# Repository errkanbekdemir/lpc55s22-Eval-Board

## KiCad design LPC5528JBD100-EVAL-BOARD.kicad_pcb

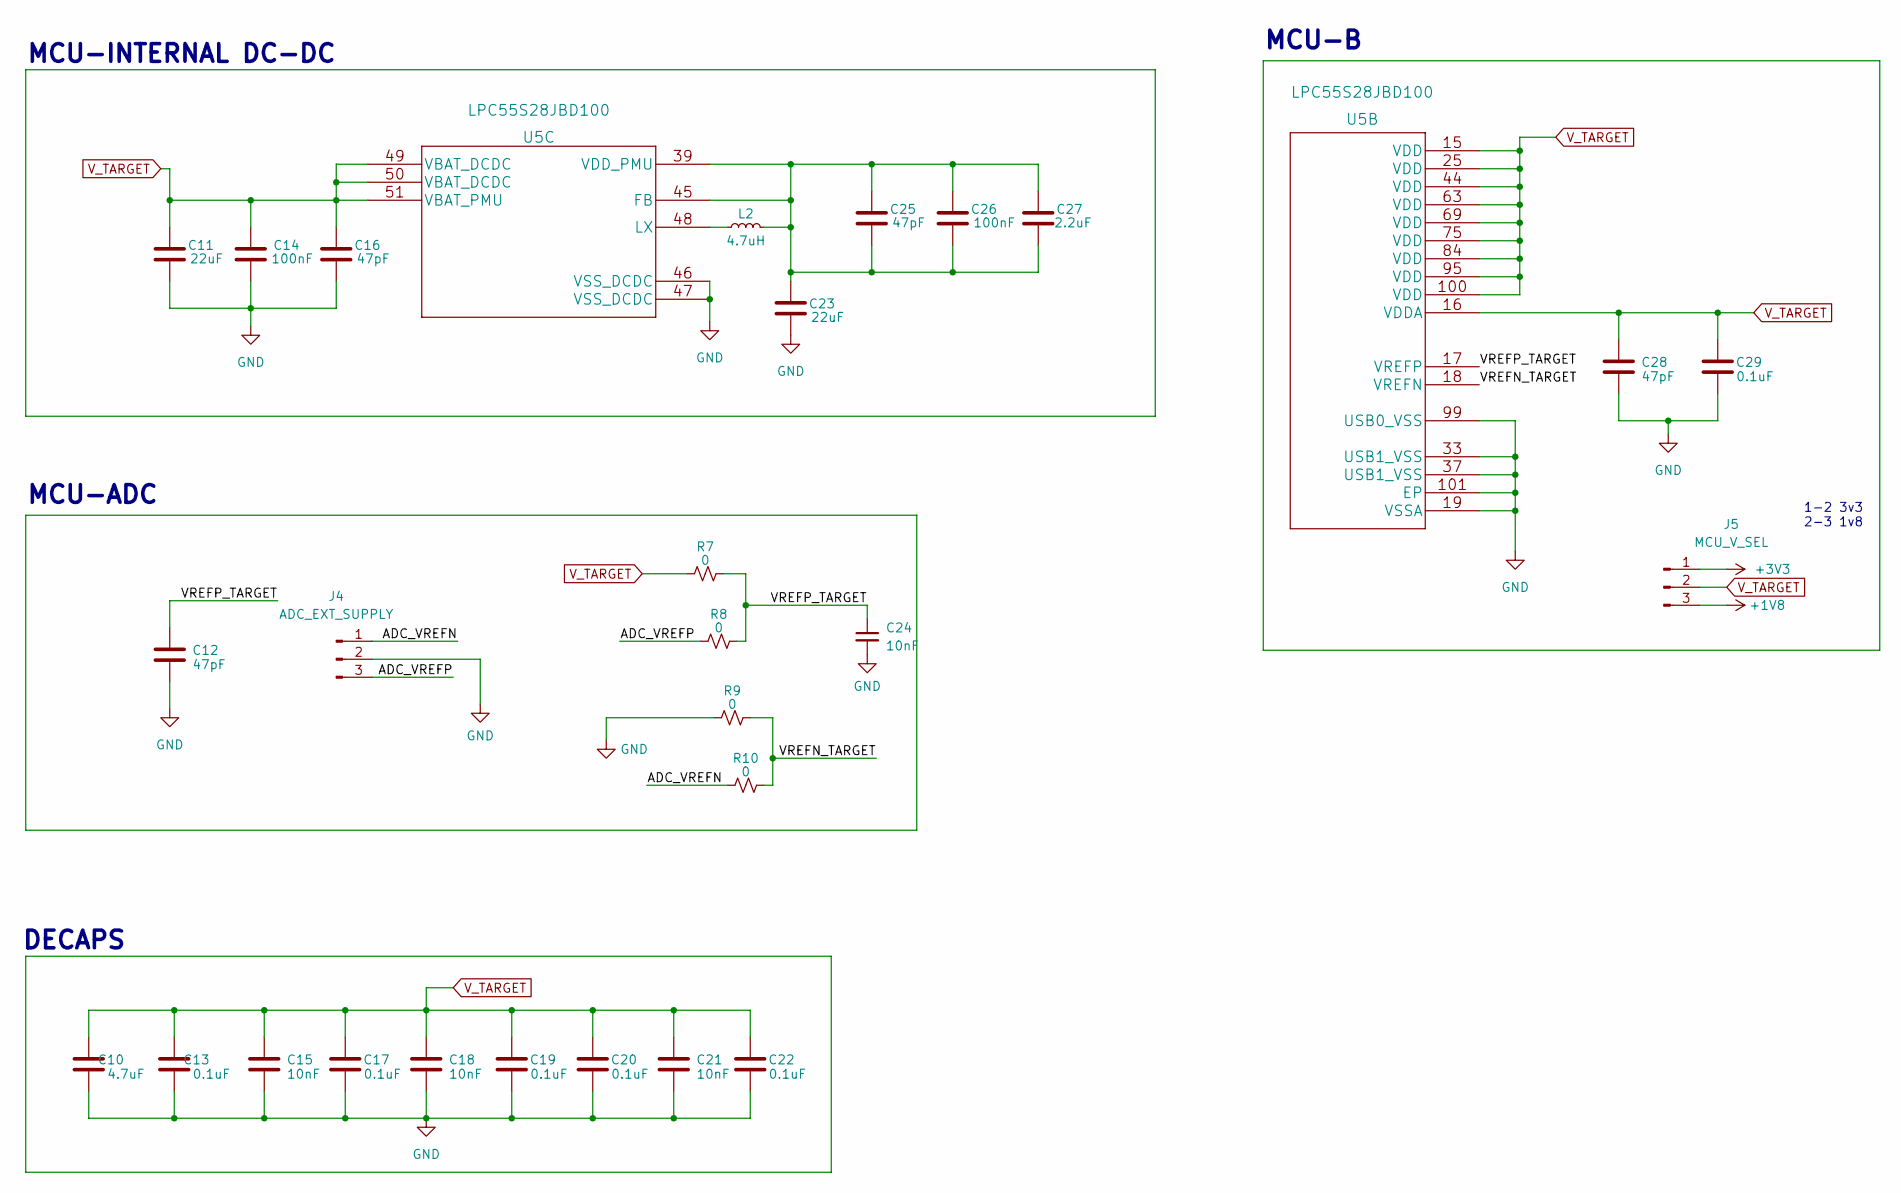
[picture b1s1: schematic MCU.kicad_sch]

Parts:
C10: 4.7uF; C_0603_1608Metric
C11, C23: 22uF; C_0603_1608Metric
C12: 47pF; R_0603_1608Metric
C13, C17, C19, C20, C22, C29: 0.1uF; C_0603_1608Metric
C14, C26: 100nF; C_0603_1608Metric
C15, C18, C21, C24: 10nF; C_0603_1608Metric
C16, C25, C28: 47pF; C_0603_1608Metric
C27: 2.2uF; C_0603_1608Metric
J4: ADC_EXT_SUPPLY; PinHeader_1x03_P2.54mm_Vertical
J5: MCU_V_SEL; PinHeader_1x03_P2.54mm_Vertical
L2: 4.7uH; L_0805_2012Metric
R7, R8, R9, R10: 0; R_0603_1608Metric
U5: LPC55S28JBD100; HLQFP100

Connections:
+1V8: J5.3; also elsewhere on the board
+3V3: J5.1; also elsewhere on the board
/MCU/ADC_VREFN: J4.1, R10.1
/MCU/ADC_VREFP: J4.3, R8.1
/MCU/VREFN_TARGET: R9.2, R10.2, U5.18 (VREFN)
/MCU/VREFP_TARGET: C12.1, C24.1, R7.2, R8.2, U5.17 (VREFP)
GND: C10.2, C11.2, C12.2, C13.2, C14.2, C15.2, C16.2, C17.2, C18.2, C19.2, C20.2, C21.2, C22.2, C23.2, C24.2, C28.2, C29.2, J4.2, R9.1, U5.19 (VSSA), U5.33 (USB1_VSS), U5.37 (USB1_VSS), U5.46 (VSS_DCDC), U5.47 (VSS_DCDC), U5.99 (USB0_VSS), U5.101 (EP); also elsewhere on the board
unnamed: C23.1, C25.1, C25.2, C26.1, C26.2, C27.1, C27.2, L2.2, U5.39 (VDD_PMU), U5.45 (FB)
unnamed: L2.1, U5.48 (LX)
V_TARGET: C10.1, C11.1, C13.1, C14.1, C15.1, C16.1, C17.1, C18.1, C19.1, C20.1, C21.1, C22.1, C28.1, C29.1, J5.2, R7.1, U5.15 (VDD), U5.16 (VDDA), U5.25 (VDD), U5.44 (VDD), U5.49 (VBAT_DCDC), U5.50 (VBAT_DCDC), U5.51 (VBAT_PMU), U5.63 (VDD), U5.69 (VDD), U5.75 (VDD), U5.84 (VDD), U5.95 (VDD), U5.100 (VDD); also elsewhere on the board

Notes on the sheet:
MCU-ADC
MCU-B
DECAPS
MCU-INTERNAL DC-DC
1-2 3v3 2-3 1v8

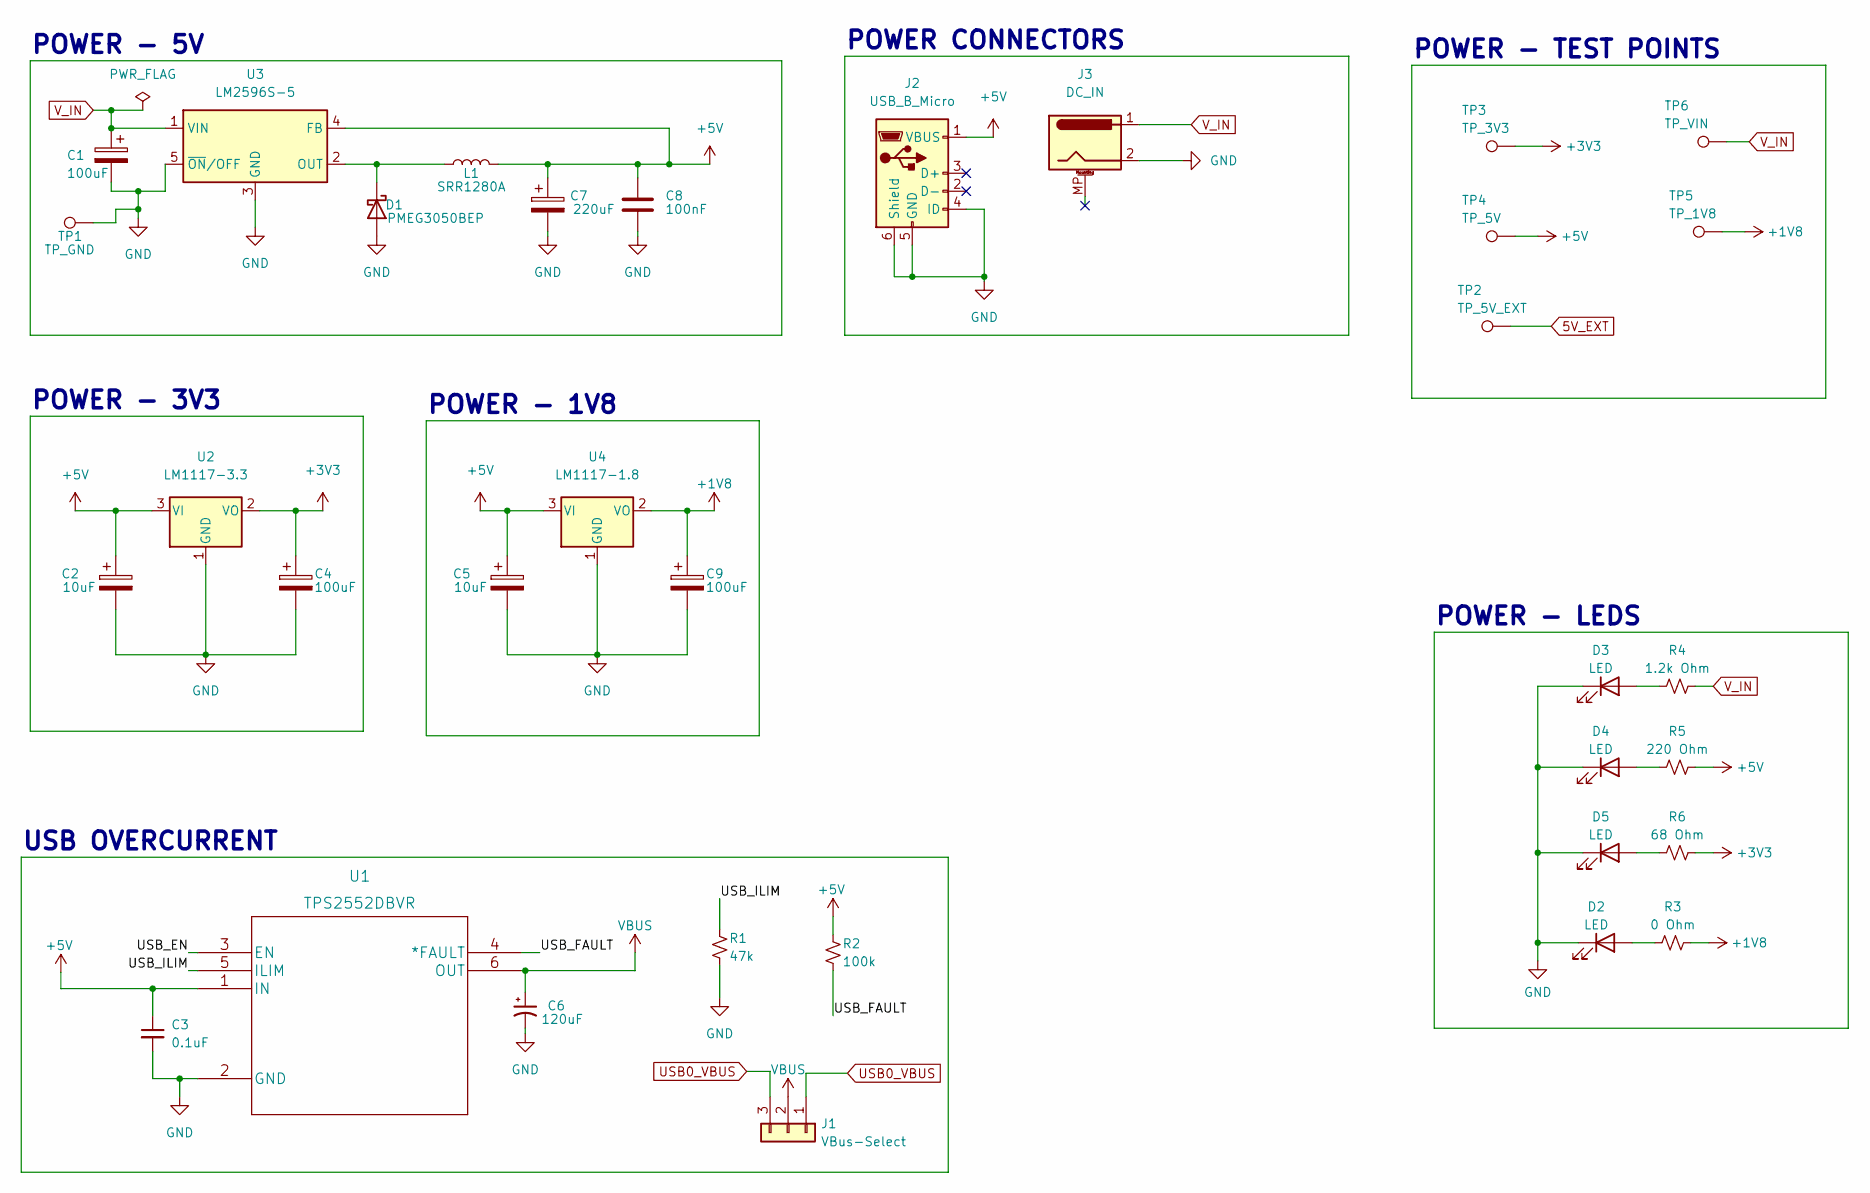
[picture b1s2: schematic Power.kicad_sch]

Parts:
C1: 100uF; CP_Elec_8x10.5
C2, C5: 10uF; CP_EIA-6032-28_Kemet-C
C3: 0.1uF; C_0603_1608Metric
C4, C9: 100uF; CP_EIA-6032-28_Kemet-C
C6: 120uF; CP_EIA-6032-28_Kemet-C
C7: 220uF; CP_EIA-6032-28_Kemet-C
C8: 100nF; C_0603_1608Metric
D1: PMEG3050BEP; D_SOD-128
D2, D3, D4, D5: LED; LED_0805_2012Metric
J1: VBus-Select; PinHeader_1x03_P2.54mm_Vertical
J2: USB_B_Micro; USB_Micro-B_Molex_47346-0001
J3: DC_IN; DC-JACK-5.5x2.1
L1: SRR1280A; L_Bourns_SRR1260
R1: 47k; R_0603_1608Metric
R2: 100k; R_0603_1608Metric
R3: 0 Ohm; R_0603_1608Metric
R4: 1.2k Ohm; R_0603_1608Metric
R5: 220 Ohm; R_0603_1608Metric
R6: 68 Ohm; R_0603_1608Metric
TP1: TP_GND; TestPoint_Pad_D1.0mm
TP2: TP_5V_EXT; TestPoint_Pad_D1.0mm
TP3: TP_3V3; TestPoint_Pad_D1.0mm
TP4: TP_5V; TestPoint_Pad_D1.0mm
TP5: TP_1V8; TestPoint_Pad_D1.0mm
TP6: TP_VIN; TestPoint_Pad_D1.0mm
U1: TPS2552DBVR
U2: LM1117-3.3; SOT-223-3_TabPin2
U3: LM2596S-5; TO-263-5_TabPin3
U4: LM1117-1.8; SOT-223-3_TabPin2

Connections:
5V_EXT: TP2.1
+1V8: C9.1, R3.2, TP5.1, U4.2 (VO); also elsewhere on the board
+3V3: C4.1, R6.2, TP3.1, U2.2 (VO); also elsewhere on the board
+5V: C2.1, C3.1, C5.1, C7.1, C8.1, J2.1 (VBUS), L1.2, R2.1, R5.2, TP4.1, U1.1 (IN), U2.3 (VI), U3.4 (FB), U4.3 (VI)
/Power/USB_EN: U1.3 (EN)
/Power/USB_FAULT: R2.2, U1.4 (*FAULT)
/Power/USB_ILIM: R1.1, U1.5 (ILIM)
GND: C1.2, C2.2, C3.2, C4.2, C5.2, C6.2, C7.2, C8.2, C9.2, D1.2 (A), D2.1 (K), D3.1 (K), D4.1 (K), D5.1 (K), J2.4 (ID), J2.5 (GND), J2.6 (Shield), J3.2, R1.2, TP1.1, U1.2 (GND), U2.1 (GND), U3.3 (GND), U3.5 (~ON/OFF), U4.1 (GND); also elsewhere on the board
unnamed: D1.1 (K), L1.1, U3.2 (OUT)
unnamed: D2.2 (A), R3.1
unnamed: D3.2 (A), R4.1
unnamed: D4.2 (A), R5.1
unnamed: D5.2 (A), R6.1
USB0_VBUS: J1.1, J1.3
VBUS: C6.1, J1.2, U1.6 (OUT)
V_IN: C1.1, J3.1, R4.2, TP6.1, U3.1 (VIN)

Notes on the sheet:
POWER CONNECTORS
POWER - 1V8
USB OVERCURRENT
POWER - 3V3
POWER - 5V
POWER - TEST POINTS
POWER - LEDS

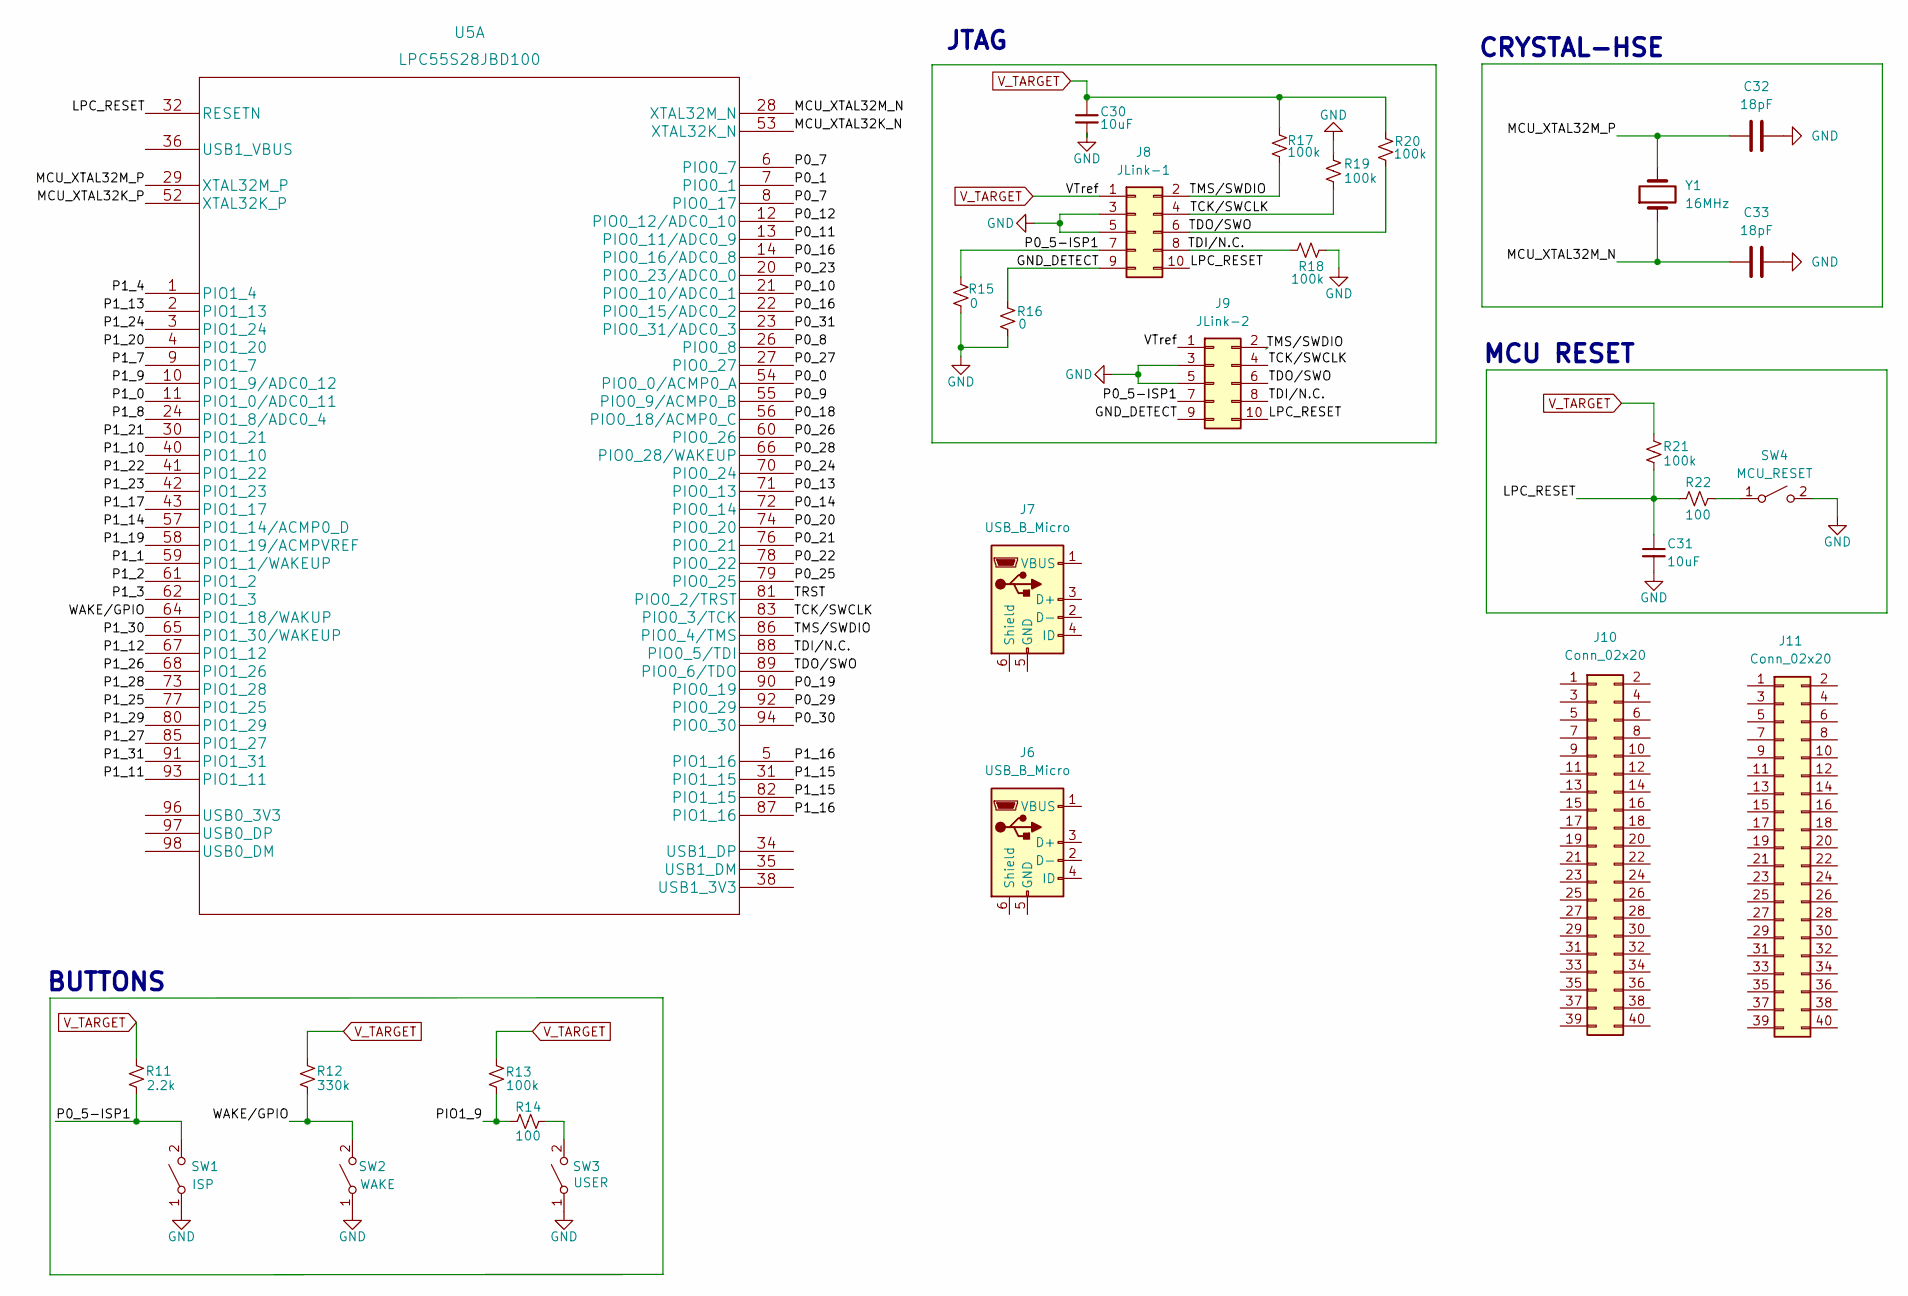
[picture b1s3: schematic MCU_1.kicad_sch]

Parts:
C30, C31: 10uF; C_0603_1608Metric
C32, C33: 18pF; C_0603_1608Metric
J6, J7: USB_B_Micro; USB_Micro-B_Molex_47346-0001
J8: JLink-1; PinHeader_2x05_P1.27mm_Vertical
J9: JLink-2; IDC-Header_2x05_P2.54mm_Vertical
J10, J11: Conn_02x20; PinSocket_2x20_P2.54mm_Vertical
R11: 2.2k; R_0603_1608Metric
R12: 330k; R_0603_1608Metric
R13, R17, R18, R19, R20, R21: 100k; R_0603_1608Metric
R14, R22: 100; R_0603_1608Metric
R15, R16: 0; R_0603_1608Metric
SW1: ISP; SW_SPST_PTS645
SW2: WAKE; SW_SPST_PTS645
SW3: USER; SW_SPST_PTS645
SW4: MCU_RESET; SW_SPST_PTS645
U5: LPC55S28JBD100; HLQFP100
Y1: 16MHz; Crystal_SMD_HC49-SD

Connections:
/MCU_1/GND_DETECT: J8.9, J9.9, R16.1
/MCU_1/LPC_RESET: C31.1, J8.10, J9.10, R21.2, R22.1, U5.32 (RESETN)
/MCU_1/MCU_XTAL32K_N: U5.53 (XTAL32K_N)
/MCU_1/MCU_XTAL32K_P: U5.52 (XTAL32K_P)
/MCU_1/MCU_XTAL32M_N: C33.1, U5.28 (XTAL32M_N), Y1.1
/MCU_1/MCU_XTAL32M_P: C32.1, U5.29 (XTAL32M_P), Y1.2
/MCU_1/P0_0: U5.54 (PIO0_0/ACMP0_A)
/MCU_1/P0_1: U5.7 (PIO0_1)
/MCU_1/P0_5-ISP1: J8.7, J9.7, R11.2, R15.1, SW1.2 (B)
/MCU_1/P0_7: U5.6 (PIO0_7), U5.8 (PIO0_17)
/MCU_1/P0_8: U5.26 (PIO0_8)
/MCU_1/P0_9: U5.55 (PIO0_9/ACMP0_B)
/MCU_1/P0_10: U5.21 (PIO0_10/ADC0_1)
/MCU_1/P0_11: U5.13 (PIO0_11/ADC0_9)
/MCU_1/P0_12: U5.12 (PIO0_12/ADC0_10)
/MCU_1/P0_13: U5.71 (PIO0_13)
/MCU_1/P0_14: U5.72 (PIO0_14)
/MCU_1/P0_16: U5.14 (PIO0_16/ADC0_8), U5.22 (PIO0_15/ADC0_2)
/MCU_1/P0_18: U5.56 (PIO0_18/ACMP0_C)
/MCU_1/P0_19: U5.90 (PIO0_19)
/MCU_1/P0_20: U5.74 (PIO0_20)
/MCU_1/P0_21: U5.76 (PIO0_21)
/MCU_1/P0_22: U5.78 (PIO0_22)
/MCU_1/P0_23: U5.20 (PIO0_23/ADC0_0)
/MCU_1/P0_24: U5.70 (PIO0_24)
/MCU_1/P0_25: U5.79 (PIO0_25)
/MCU_1/P0_26: U5.60 (PIO0_26)
/MCU_1/P0_27: U5.27 (PIO0_27)
/MCU_1/P0_28: U5.66 (PIO0_28/WAKEUP)
/MCU_1/P0_29: U5.92 (PIO0_29)
/MCU_1/P0_30: U5.94 (PIO0_30)
/MCU_1/P0_31: U5.23 (PIO0_31/ADC0_3)
/MCU_1/P1_0: U5.11 (PIO1_0/ADC0_11)
/MCU_1/P1_1: U5.59 (PIO1_1/WAKEUP)
/MCU_1/P1_2: U5.61 (PIO1_2)
/MCU_1/P1_3: U5.62 (PIO1_3)
/MCU_1/P1_4: U5.1 (PIO1_4)
/MCU_1/P1_7: U5.9 (PIO1_7)
/MCU_1/P1_8: U5.24 (PIO1_8/ADC0_4)
/MCU_1/P1_9: U5.10 (PIO1_9/ADC0_12)
/MCU_1/P1_10: U5.40 (PIO1_10)
/MCU_1/P1_11: U5.93 (PIO1_11)
/MCU_1/P1_12: U5.67 (PIO1_12)
/MCU_1/P1_13: U5.2 (PIO1_13)
/MCU_1/P1_14: U5.57 (PIO1_14/ACMP0_D)
/MCU_1/P1_15: U5.31 (PIO1_15), U5.82 (PIO1_15)
/MCU_1/P1_16: U5.5 (PIO1_16), U5.87 (PIO1_16)
/MCU_1/P1_17: U5.43 (PIO1_17)
/MCU_1/P1_19: U5.58 (PIO1_19/ACMPVREF)
/MCU_1/P1_20: U5.4 (PIO1_20)
/MCU_1/P1_21: U5.30 (PIO1_21)
/MCU_1/P1_22: U5.41 (PIO1_22)
/MCU_1/P1_23: U5.42 (PIO1_23)
/MCU_1/P1_24: U5.3 (PIO1_24)
/MCU_1/P1_25: U5.77 (PIO1_25)
/MCU_1/P1_26: U5.68 (PIO1_26)
/MCU_1/P1_27: U5.85 (PIO1_27)
/MCU_1/P1_28: U5.73 (PIO1_28)
/MCU_1/P1_29: U5.80 (PIO1_29)
/MCU_1/P1_30: U5.65 (PIO1_30/WAKEUP)
/MCU_1/P1_31: U5.91 (PIO1_31)
/MCU_1/PIO1_9: R13.2, R14.1
/MCU_1/TCK/SWCLK: J8.4, J9.4, R19.2, U5.83 (PIO0_3/TCK)
/MCU_1/TDI/N.C.: J8.8, J9.8, R18.1, U5.88 (PIO0_5/TDI)
/MCU_1/TDO/SWO: J8.6, J9.6, R20.1, U5.89 (PIO0_6/TDO)
/MCU_1/TMS/SWDIO: J8.2, J9.2, R17.1, U5.86 (PIO0_4/TMS)
/MCU_1/TRST: U5.81 (PIO0_2/TRST)
/MCU_1/WAKE/GPIO: R12.2, SW2.2 (B), U5.64 (PIO1_18/WAKUP)
GND: C30.2, C31.2, C32.2, C33.2, J8.3, J8.5, J9.3, J9.5, R15.2, R16.2, R18.2, R19.1, SW1.1 (A), SW2.1 (A), SW3.1 (A), SW4.2 (B); also elsewhere on the board
unnamed: R14.2, SW3.2 (B)
unnamed: R22.2, SW4.1 (A)
V_TARGET: C30.1, J8.1, J9.1, R11.1, R12.1, R13.1, R17.2, R20.2, R21.1; also elsewhere on the board

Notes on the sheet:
JTAG
BUTTONS
CRYSTAL-HSE
MCU RESET

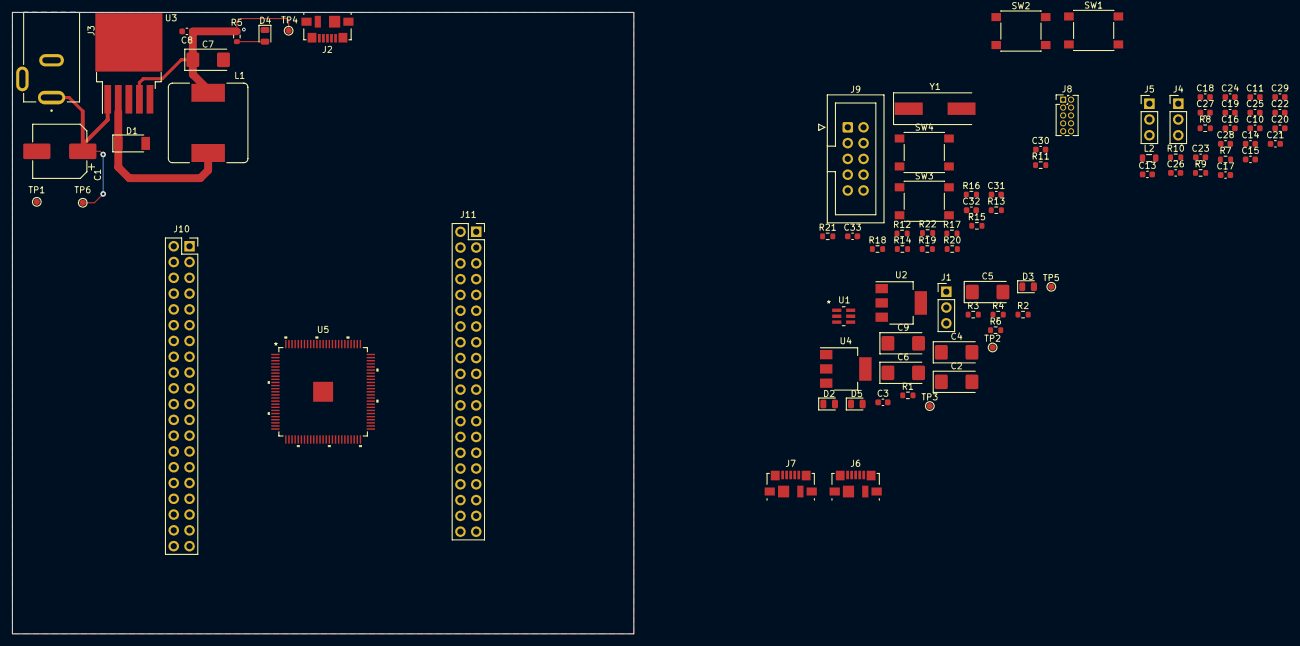
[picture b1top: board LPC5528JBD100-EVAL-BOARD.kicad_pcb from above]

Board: 2 copper layers, 100.0 x 100.0 mm, 88 parts (0 on the bottom side), 38 nets.

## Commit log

2022-10-31 USB Power switch eklendi. Devresi tamamlanacak
2022-11-02 LM2596 Layout oluşturuldu, USB Power switch tarafı eksik
2022-11-02 LM2596 Layout ve yollar çizildi
2022-11-04 LM2596 layout değiştirildi
2022-11-04 Power ledler eklendi
2022-11-08 USB Current limiting devresi tamamlanacak. ADC bağlantıları yapılıyor
2022-11-08 MCU bölümlere ayrýldý
2022-11-09 Reset devresi eklenecek.
2022-11-10 JTAG bağlantıları tamamlanacak
2022-11-11 ISP Boot eklenecek
2022-11-14 Schematic updated
2022-11-15 JTAG swo pin pull down yapıldı
2022-11-17 Butonlar eklendi
2022-11-17 Butonlar eklendi ve usb eklendi
2022-11-18 Pin labelları eklendi

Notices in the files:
parts and their libraries:
Copyright 2021 Accelerated Designs. All rights reserved.
